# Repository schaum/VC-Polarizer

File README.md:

# VC-Polarizer

This VC Polarizer hardware is a shrinked clone of the [Mutable Blinds PCB](http://mutable-instruments.net/modules/blinds) and published under the same license: cc-by-sa-3.0.

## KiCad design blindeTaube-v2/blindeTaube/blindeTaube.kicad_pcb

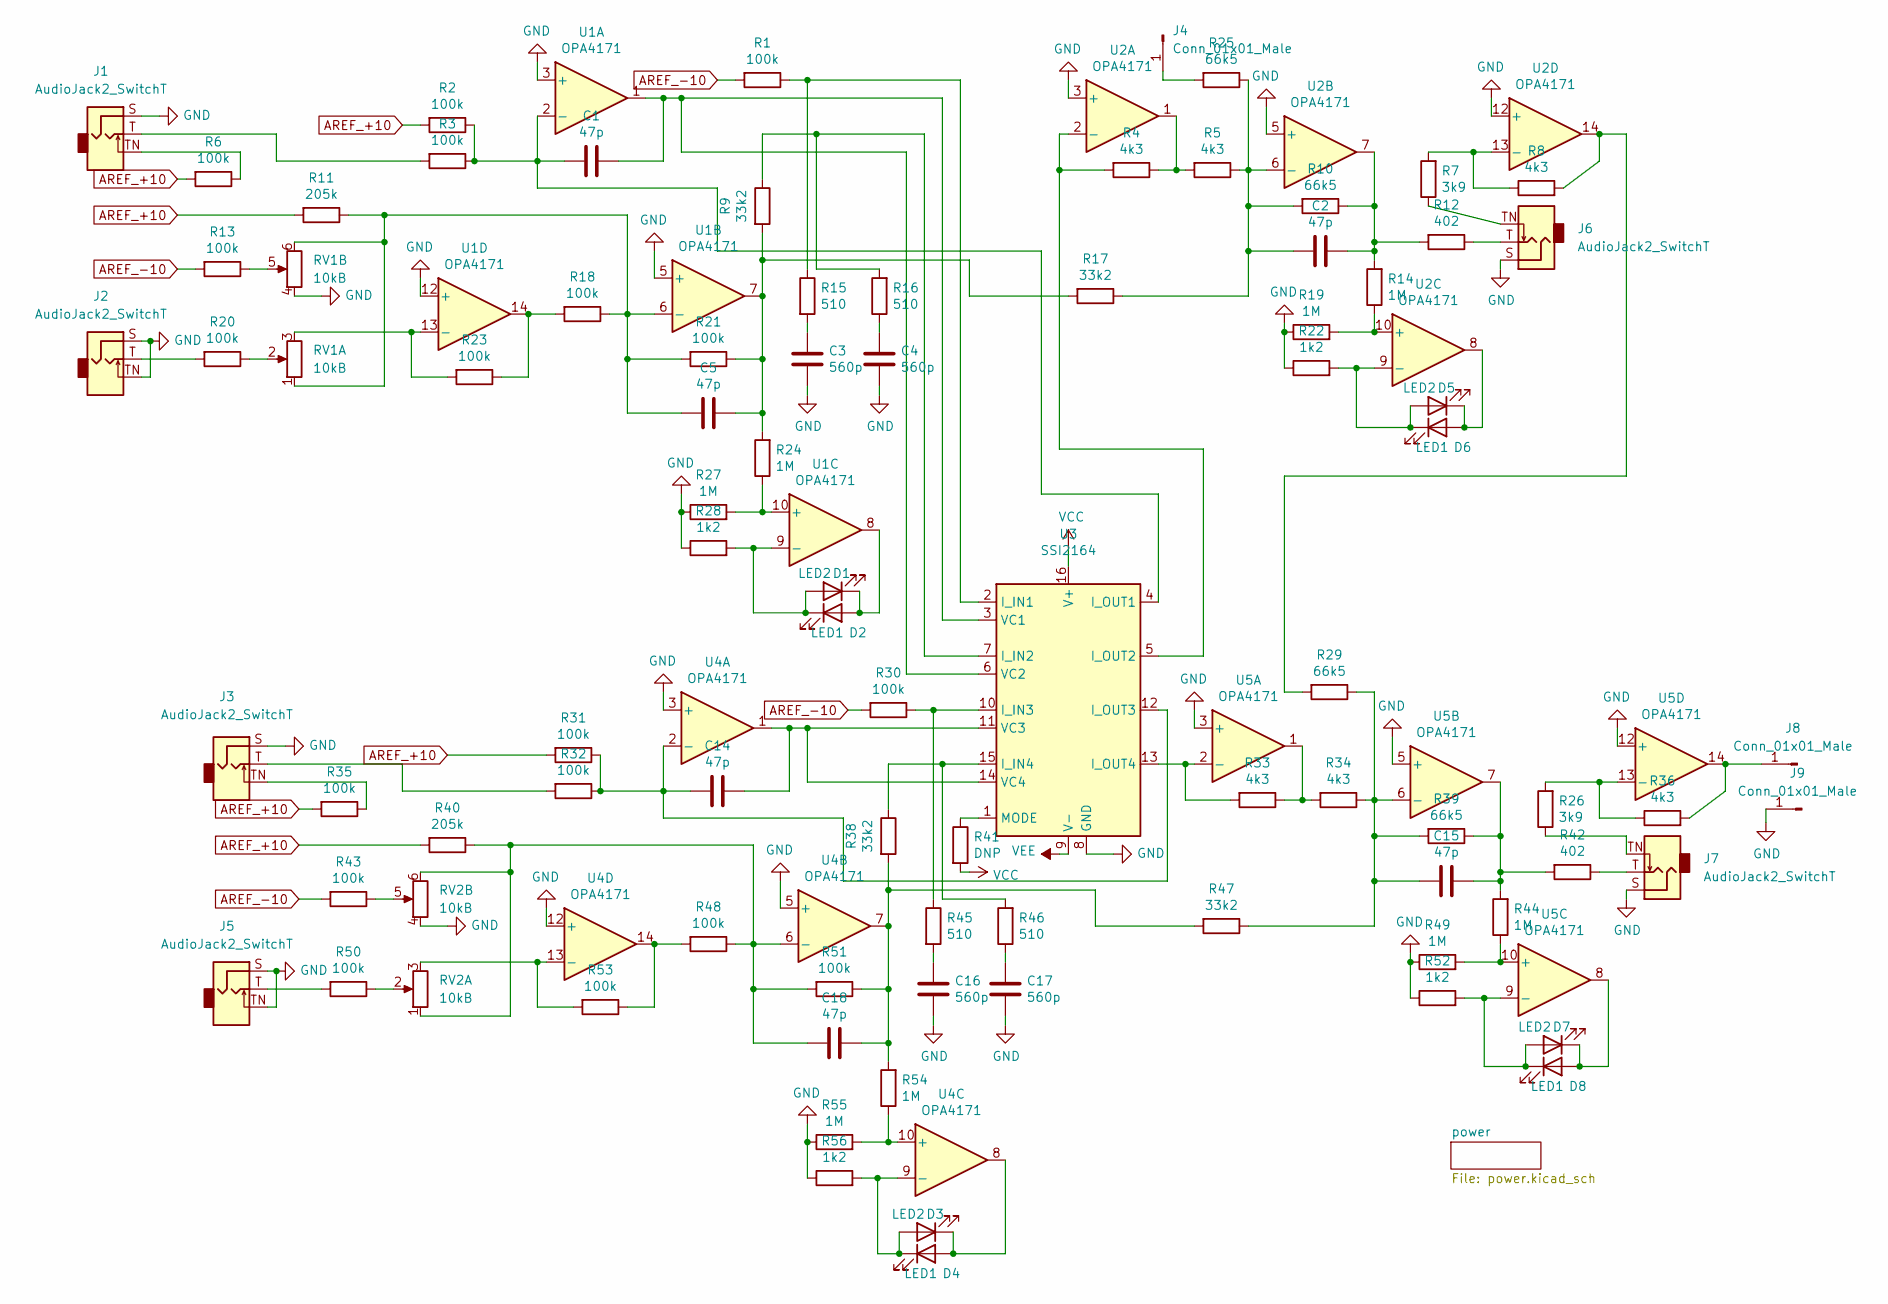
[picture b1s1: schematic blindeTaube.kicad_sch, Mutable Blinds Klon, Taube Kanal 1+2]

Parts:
C1, C2, C5, C14, C15, C18: 47p; C_0805_2012Metric_Pad1.18x1.45mm_HandSolder
C3, C4, C16, C17: 560p; C_0805_2012Metric_Pad1.18x1.45mm_HandSolder
D1, D3, D5, D7: LED2; LED_2106Metric_Pad1.1x0.5mm_HandSolder
D2, D4, D6, D8: LED1; LED_2106Metric_Pad1.1x0.5mm_HandSolder
J1, J2, J3, J5, J6, J7: AudioJack2_SwitchT; Jack_3.5mm_PJ323_Horizontal
J4, J8, J9: Conn_01x01_Male; PinHeader_1x01_P2.54mm_Vertical
R1, R2, R3, R6, R13, R18, R20, R21, R23, R30, R31, R32, R35, R43, R48, R50, R51, R53: 100k; R_0805_2012Metric_Pad1.20x1.40mm_HandSolder
R4, R5, R8, R33, R34, R36: 4k3; R_0805_2012Metric_Pad1.20x1.40mm_HandSolder
R7, R26: 3k9; R_0805_2012Metric_Pad1.20x1.40mm_HandSolder
R9, R17, R38, R47: 33k2; R_0805_2012Metric_Pad1.20x1.40mm_HandSolder
R10, R25, R29, R39: 66k5; R_0805_2012Metric_Pad1.20x1.40mm_HandSolder
R11, R40: 205k; R_0805_2012Metric_Pad1.20x1.40mm_HandSolder
R12, R42: 402; R_0805_2012Metric_Pad1.20x1.40mm_HandSolder
R14, R19, R24, R27, R44, R49, R54, R55: 1M; R_0805_2012Metric_Pad1.20x1.40mm_HandSolder
R15, R16, R45, R46: 510; R_0805_2012Metric_Pad1.20x1.40mm_HandSolder
R22, R28, R52, R56: 1k2; R_0805_2012Metric_Pad1.20x1.40mm_HandSolder
R41: DNP; R_0805_2012Metric_Pad1.20x1.40mm_HandSolder
RV1, RV2: 10kB; Potentiometer_Alps_RK097_Dual_Horizontal
U1, U2, U4, U5: OPA4171; SOIC-14_3.9x8.7mm_P1.27mm
U3: SSI2164; SOIC-16_3.9x9.9mm_P1.27mm

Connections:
AREF_+10: R2.2, R6.2, R11.2, R31.2, R35.2, R40.2; also elsewhere on the board
AREF_-10: R1.2, R13.2, R30.2, R43.2; also elsewhere on the board
GND: C3.1, C4.1, C16.1, C17.1, J1.S, J2.S, J2.TN, J3.S, J5.S, J5.TN, J6.S, J7.S, J9.1, R19.1, R22.1, R27.1, R28.1, R49.1, R52.1, R55.1, R56.1, RV1.4, RV2.4, U1.3 (+), U1.5 (+), U1.12 (+), U2.3 (+), U2.5 (+), U2.12 (+), U3.8 (GND), U4.3 (+), U4.5 (+), U4.12 (+), U5.3 (+), U5.5 (+), U5.12 (+); also elsewhere on the board
unnamed: C1.1, U1.1, U3.3 (VC1), U3.6 (VC2)
unnamed: C1.2, R2.1, R3.1, U1.2 (-), U3.4 (I_OUT1)
unnamed: C2.1, R10.1, R12.2, R14.2, U2.7
unnamed: C2.2, R5.1, R10.2, R17.1, R25.1, U2.6 (-)
unnamed: C3.2, R15.2
unnamed: C4.2, R16.1
unnamed: C5.1, R9.2, R17.2, R21.1, R24.2, U1.7
unnamed: C5.2, R11.1, R18.1, R21.2, RV1.1, RV1.6, U1.6 (-)
unnamed: C14.1, U3.11 (VC3), U3.14 (VC4), U4.1
unnamed: C14.2, R31.1, R32.1, U3.12 (I_OUT3), U4.2 (-)
unnamed: C15.1, R39.1, R42.2, R44.2, U5.7
unnamed: C15.2, R29.1, R34.1, R39.2, R47.1, U5.6 (-)
unnamed: C16.2, R45.2
unnamed: C17.2, R46.1
unnamed: C18.1, R38.2, R47.2, R51.1, R54.2, U4.7
unnamed: C18.2, R40.1, R48.1, R51.2, RV2.1, RV2.6, U4.6 (-)
unnamed: D1.1 (K), D2.2 (A), U1.8
unnamed: D1.2 (A), D2.1 (K), R28.2, U1.9 (-)
unnamed: D3.1 (K), D4.2 (A), U4.8
unnamed: D3.2 (A), D4.1 (K), R56.2, U4.9 (-)
unnamed: D5.1 (K), D6.2 (A), U2.8
unnamed: D5.2 (A), D6.1 (K), R22.2, U2.9 (-)
unnamed: D7.1 (K), D8.2 (A), U5.8
unnamed: D7.2 (A), D8.1 (K), R52.2, U5.9 (-)
unnamed: J1.T, R3.2
unnamed: J1.TN, R6.1
unnamed: J2.T, R20.2
unnamed: J3.T, R32.2
unnamed: J3.TN, R35.1
unnamed: J5.T, R50.2
unnamed: J6.T, R12.1
unnamed: J6.TN, R7.1
unnamed: J7.T, R42.1
unnamed: J7.TN, R26.1
unnamed: R1.1, R15.1, U3.2 (I_IN1)
unnamed: R4.1, R5.2, U2.1
unnamed: R4.2, U2.2 (-), U3.5 (I_OUT2)
unnamed: R7.2, R8.1, U2.13 (-)
unnamed: R13.1, RV1.5
unnamed: R14.1, R19.2, U2.10 (+)
unnamed: R9.1, R16.2, U3.7 (I_IN2)
unnamed: R18.2, R23.1, U1.14
unnamed: R20.1, RV1.2
unnamed: R23.2, RV1.3, U1.13 (-)
unnamed: R24.1, R27.2, U1.10 (+)
unnamed: J4.1, R25.2
unnamed: R8.2, R29.2, U2.14
unnamed: R30.1, R45.1, U3.10 (I_IN3)
unnamed: R33.1, R34.2, U5.1
unnamed: R33.2, U3.13 (I_OUT4), U5.2 (-)
unnamed: R38.1, R46.2, U3.15 (I_IN4)
unnamed: R41.1, U3.1 (MODE)
unnamed: R43.1, RV2.5
unnamed: R44.1, R49.2, U5.10 (+)
unnamed: R48.2, R53.1, U4.14
unnamed: R50.1, RV2.2
unnamed: R53.2, RV2.3, U4.13 (-)
unnamed: R54.1, R55.2, U4.10 (+)
unnamed: R26.2, R36.1, U5.13 (-)
unnamed: J8.1, R36.2, U5.14
VCC: R41.2, U3.16 (V+); also elsewhere on the board
VEE: U3.9 (V-); also elsewhere on the board

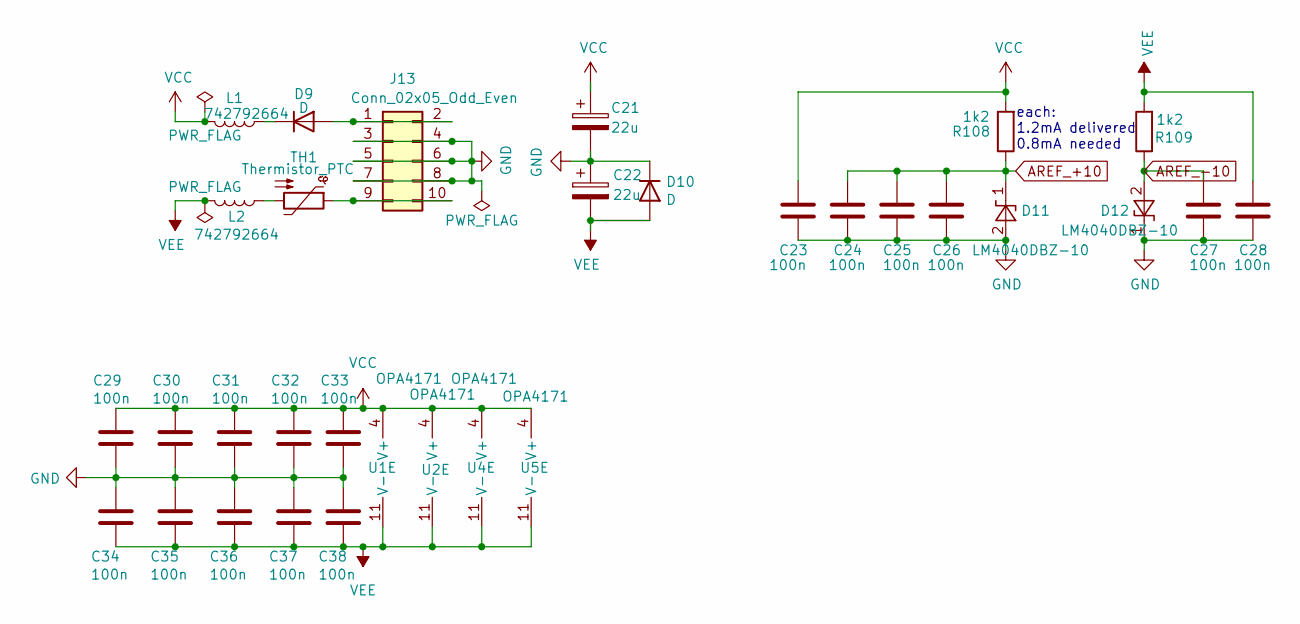
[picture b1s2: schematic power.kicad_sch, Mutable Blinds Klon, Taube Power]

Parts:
C21, C22: 22u; CP_Radial_D5.0mm_P2.50mm
C23, C24, C25, C26, C27, C28, C29, C30, C31, C32, C33, C34, C35, C36, C37, C38: 100n; C_0805_2012Metric_Pad1.18x1.45mm_HandSolder
D9, D10: D; D_SMA_Handsoldering
D11, D12: LM4040DBZ-10; SOT-23_Handsoldering
J13: Conn_02x05_Odd_Even; PinHeader_2x05_P2.54mm_Vertical
L1, L2: 742792664; L_0603_1608Metric_Pad1.05x0.95mm_HandSolder
R108, R109: 1k2; R_0805_2012Metric_Pad1.20x1.40mm_HandSolder
TH1: Thermistor_PTC; R_1206_3216Metric_Pad1.30x1.75mm_HandSolder
U1, U2, U4, U5: OPA4171; SOIC-14_3.9x8.7mm_P1.27mm

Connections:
AREF_+10: C24.2, C25.2, C26.2, D11.1 (K), R108.1; also elsewhere on the board
AREF_-10: C27.2, D12.2 (A), R109.1; also elsewhere on the board
GND: C21.2, C22.1, C23.1, C24.1, C25.1, C26.1, C27.1, C28.1, C29.1, C30.1, C31.1, C32.1, C33.1, C34.2, C35.2, C36.2, C37.2, C38.2, D10.1 (K), D11.2 (A), D12.1 (K), J13.3, J13.4, J13.5, J13.6, J13.7, J13.8; also elsewhere on the board
unnamed: D9.1 (K), L1.1
unnamed: D9.2 (A), J13.1, J13.2
unnamed: J13.9, J13.10, TH1.1
unnamed: L2.1, TH1.2
VCC: C21.1, C23.2, C29.2, C30.2, C31.2, C32.2, C33.2, L1.2, R108.2, U1.4 (V+), U2.4 (V+), U4.4 (V+), U5.4 (V+); also elsewhere on the board
VEE: C22.2, C28.2, C34.1, C35.1, C36.1, C37.1, C38.1, D10.2 (A), L2.2, R109.2, U1.11 (V-), U2.11 (V-), U4.11 (V-), U5.11 (V-); also elsewhere on the board

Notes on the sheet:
each: 1.2mA delivered 0.8mA needed

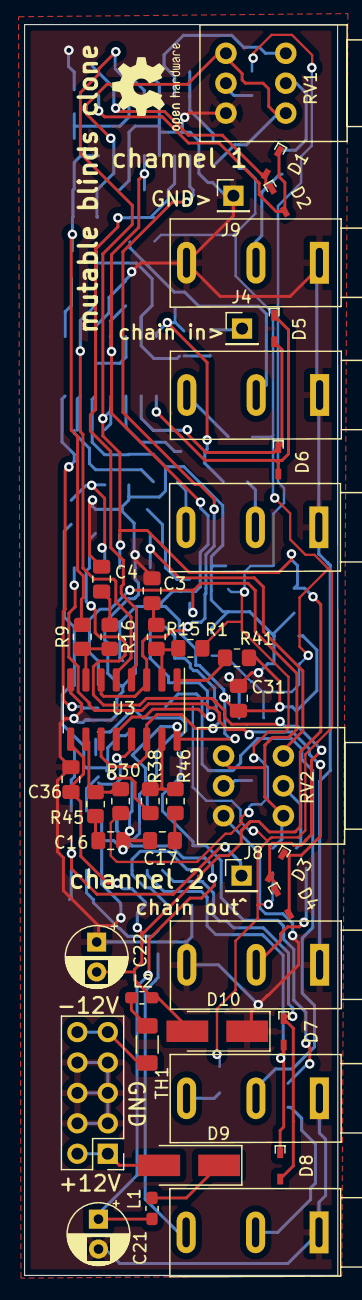
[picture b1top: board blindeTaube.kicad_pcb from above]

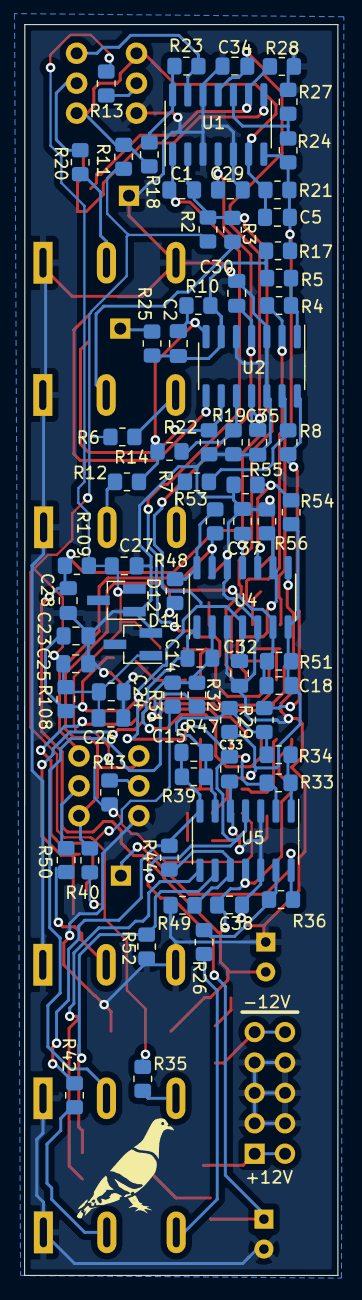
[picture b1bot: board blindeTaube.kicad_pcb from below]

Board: 2 copper layers, 26.2 x 104.5 mm, 117 parts (74 on the bottom side), 69 nets.

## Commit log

2022-08-12 initial gitignore and Readme
2022-08-12 add Version 1 and Version 2 of the Polarizer KiCad-Projects
2022-08-12 insert 3D-Screenshots into Readme
2022-08-15 move potentiometers a little bit to the edge of the board
